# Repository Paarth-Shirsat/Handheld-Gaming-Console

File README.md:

# Handheld Gaming Console

---

A Custom STM32-based Board that runs simple games on an LCD, with various peripherals such as IMU, DF-Player Mini, Buttons, Joystick and a Power System.

## PCB Iterations
---
### OLD PCB
---

### NEW PCB
---

## Table Of Contents

---

- [About The Project](#about-the-project)
    - [Tech Stack](#tech-stack)
    - [File Structure](#file-structure)
- [Getting Started](#getting-started)
    - [Prerequisites](#prerequisites)
        - Hardware
        - Software
    - [Installation](#installation)
- [Usage](#usage)
- [Results And Demo](#results-and-demo)
- [Future Work](#future-work)
- [Contributors](#contributors)
- [Acknowledgements And Resources](#acknowledgements-and-resources)

## About The Project

---

The Handheld Gaming Console is a custom made Printed Circuit Board which utilizes STM32F407VGT6 as its MCU controlling all of the peripherals. The firmware involves setting up all the components and utilizing them to run simple games with the help of controlling hardware such as buttons, joystick and IMU.
The firmware for this project is a bare-metal implementation built on a Hardware Abstraction Layer (HAL). This project is designed to provide hands-on experience and a deep understanding of the embedded development workflow.

This repository will provide all the firmware, PCB files, and steps to use those.

### Tech Stack

---

### File Structure

---

```jsx
Handheld-Gaming-Console/
├── DFPLAYER/
│   ├── dfplayer.c
│   └── dfplayer.h
│
├── HANDHELD/
│   ├── ASSETS/
│   ├── DRIVERS/
│   ├── SRC/
│   └── README.md
│
├── HandHeld-Gaming-Console/
│   ├── .settings/
│   ├── Core/
│   ├── Debug/
│   ├── Drivers/
│   ├── .cproject
│   ├── .mxproject
│   ├── .project
│   ├── HandHeld-Gaming-Console.ioc
│   ├── STM32F407VGTX_FLASH.ld
│   └── STM32F407VGTX_RAM.ld
│
├── Handheld-Nucleo/
│   ├── .settings/
│   ├── Core/
│   ├── Debug/
│   ├── Drivers/
│   ├── CMSIS/
│   ├── GAME/
│   ├── GAME2/
│   ├── MPU6050/
│   ├── STM32F4xx_HAL_Driver/
│   ├── TFT/
│   ├── .cproject
│   ├── .mxproject
│   ├── .project
│   ├── Handheld-Nucleo Debug.launch
│   ├── Handheld-Nucleo.ioc
│   ├── STM32F401RETX_FLASH.ld
│   └── STM32F401RETX_RAM.ld
│
├── PCB Files/
│   ├── HGC PCB.kicad_pcb
│   ├── HGC PROJECT.kicad_pro
│   └── HGC SCHEMATIC.kicad_sch
│
├── UART/
│   ├── uart.c
│   └── uart.h
│
└── README.md
```

## Getting Started

---

### Prerequisites

---

- Hardware
    - STM32 Microcontroller (STM32 Bluepill or Nucleo-F401RE for development)
    - ST-Link V2 or USB-to-TTL adapter (for testing/debugging)
    - Display Driver: ILI9341
    - IMU: MPU6050 (Integrated 6-axis MotionTracking device)
    - MP3 Module: DF-Player Mini
    - Joystick and Buttons
    - Speaker
- Software
    - STM32CubeIDE
    - STM32CubeProgrammer
    - PuTTY (For Serial Monitor)
    - KiCad

### Installation

---

1. Clone the repository

```jsx
git clone https://github.com/Paarth-Shirsat/Handheld-Gaming-Console.git
```

## Usage

---

Steps to flash firmware

1. Connect the console (PCB) to your computer via USB to type C cable.
2. Start the STM32CubeProgrammer.
- By using UART
    1. Select ‘UART’ from the drop-down in the top right. Select the port and set baudrate to ‘115200’ Bd.
    2. Go to ‘Erasing & Programming’ section from the far left part.
    3. Select file path of the ‘.bin’ file from the project folder (search in the ‘Debug’ folder). 
    4. Now, set the BOOT0 pin to high by flicking the switch and click ‘Connect’.
    5. After connecting successfully, click on the ‘Start Programming’ option to start uploading the firmware. A few pop-ups would appear and the board will disconnect automatically.
    6. Now, set the BOOT0 pin to low by again flicking the switch to initial position. Press the ‘Reset’ button on the PCB. You can safely remove the USB to type C cable.
- By using ST-Link
    1. Select ‘UART’ from the drop-down in the top right. Select ‘Serial Number’ and set ‘Port’ as SWD (Serial Wire Debug).
    2. Go to ‘Erasing & Programming’ section from the far left part.
    3. Select file path of the ‘.bin’ file from the project folder (search in the ‘Debug’ folder). 
    4. After the pop-up for flashing of firmware successfully comes, you can safely remove the USB to type C cable.

## Results And Demo

---

Videos of working prototypes are as follows:

Video of Game’s working:

## Future Work

---

- [ ]  Addition of sound system

## Contributors

---

- [Ashish Nerlekar](https://github.com/ashish4225)
- [Mustafa T. R.](https://github.com/mt-tass)
- [Paarth Shirsat](https://github.com/Paarth-Shirsat)

## Acknowledgements And Resources

---

- SRA VJTI Eklavya 2025
- Mentors
    - [Vishal Mutha](https://github.com/Vishal-Mutha)
    - [Piyush Patle](https://github.com/PiyushPatle26)
    - [Shaurya Rane](https://github.com/shauryarane05)
- Resources
    - Datasheets for MCU and peripherals utilized.
    - Repository for ILI9341 Library: [Repository Link](https://github.com/afiskon/stm32-ili9341)

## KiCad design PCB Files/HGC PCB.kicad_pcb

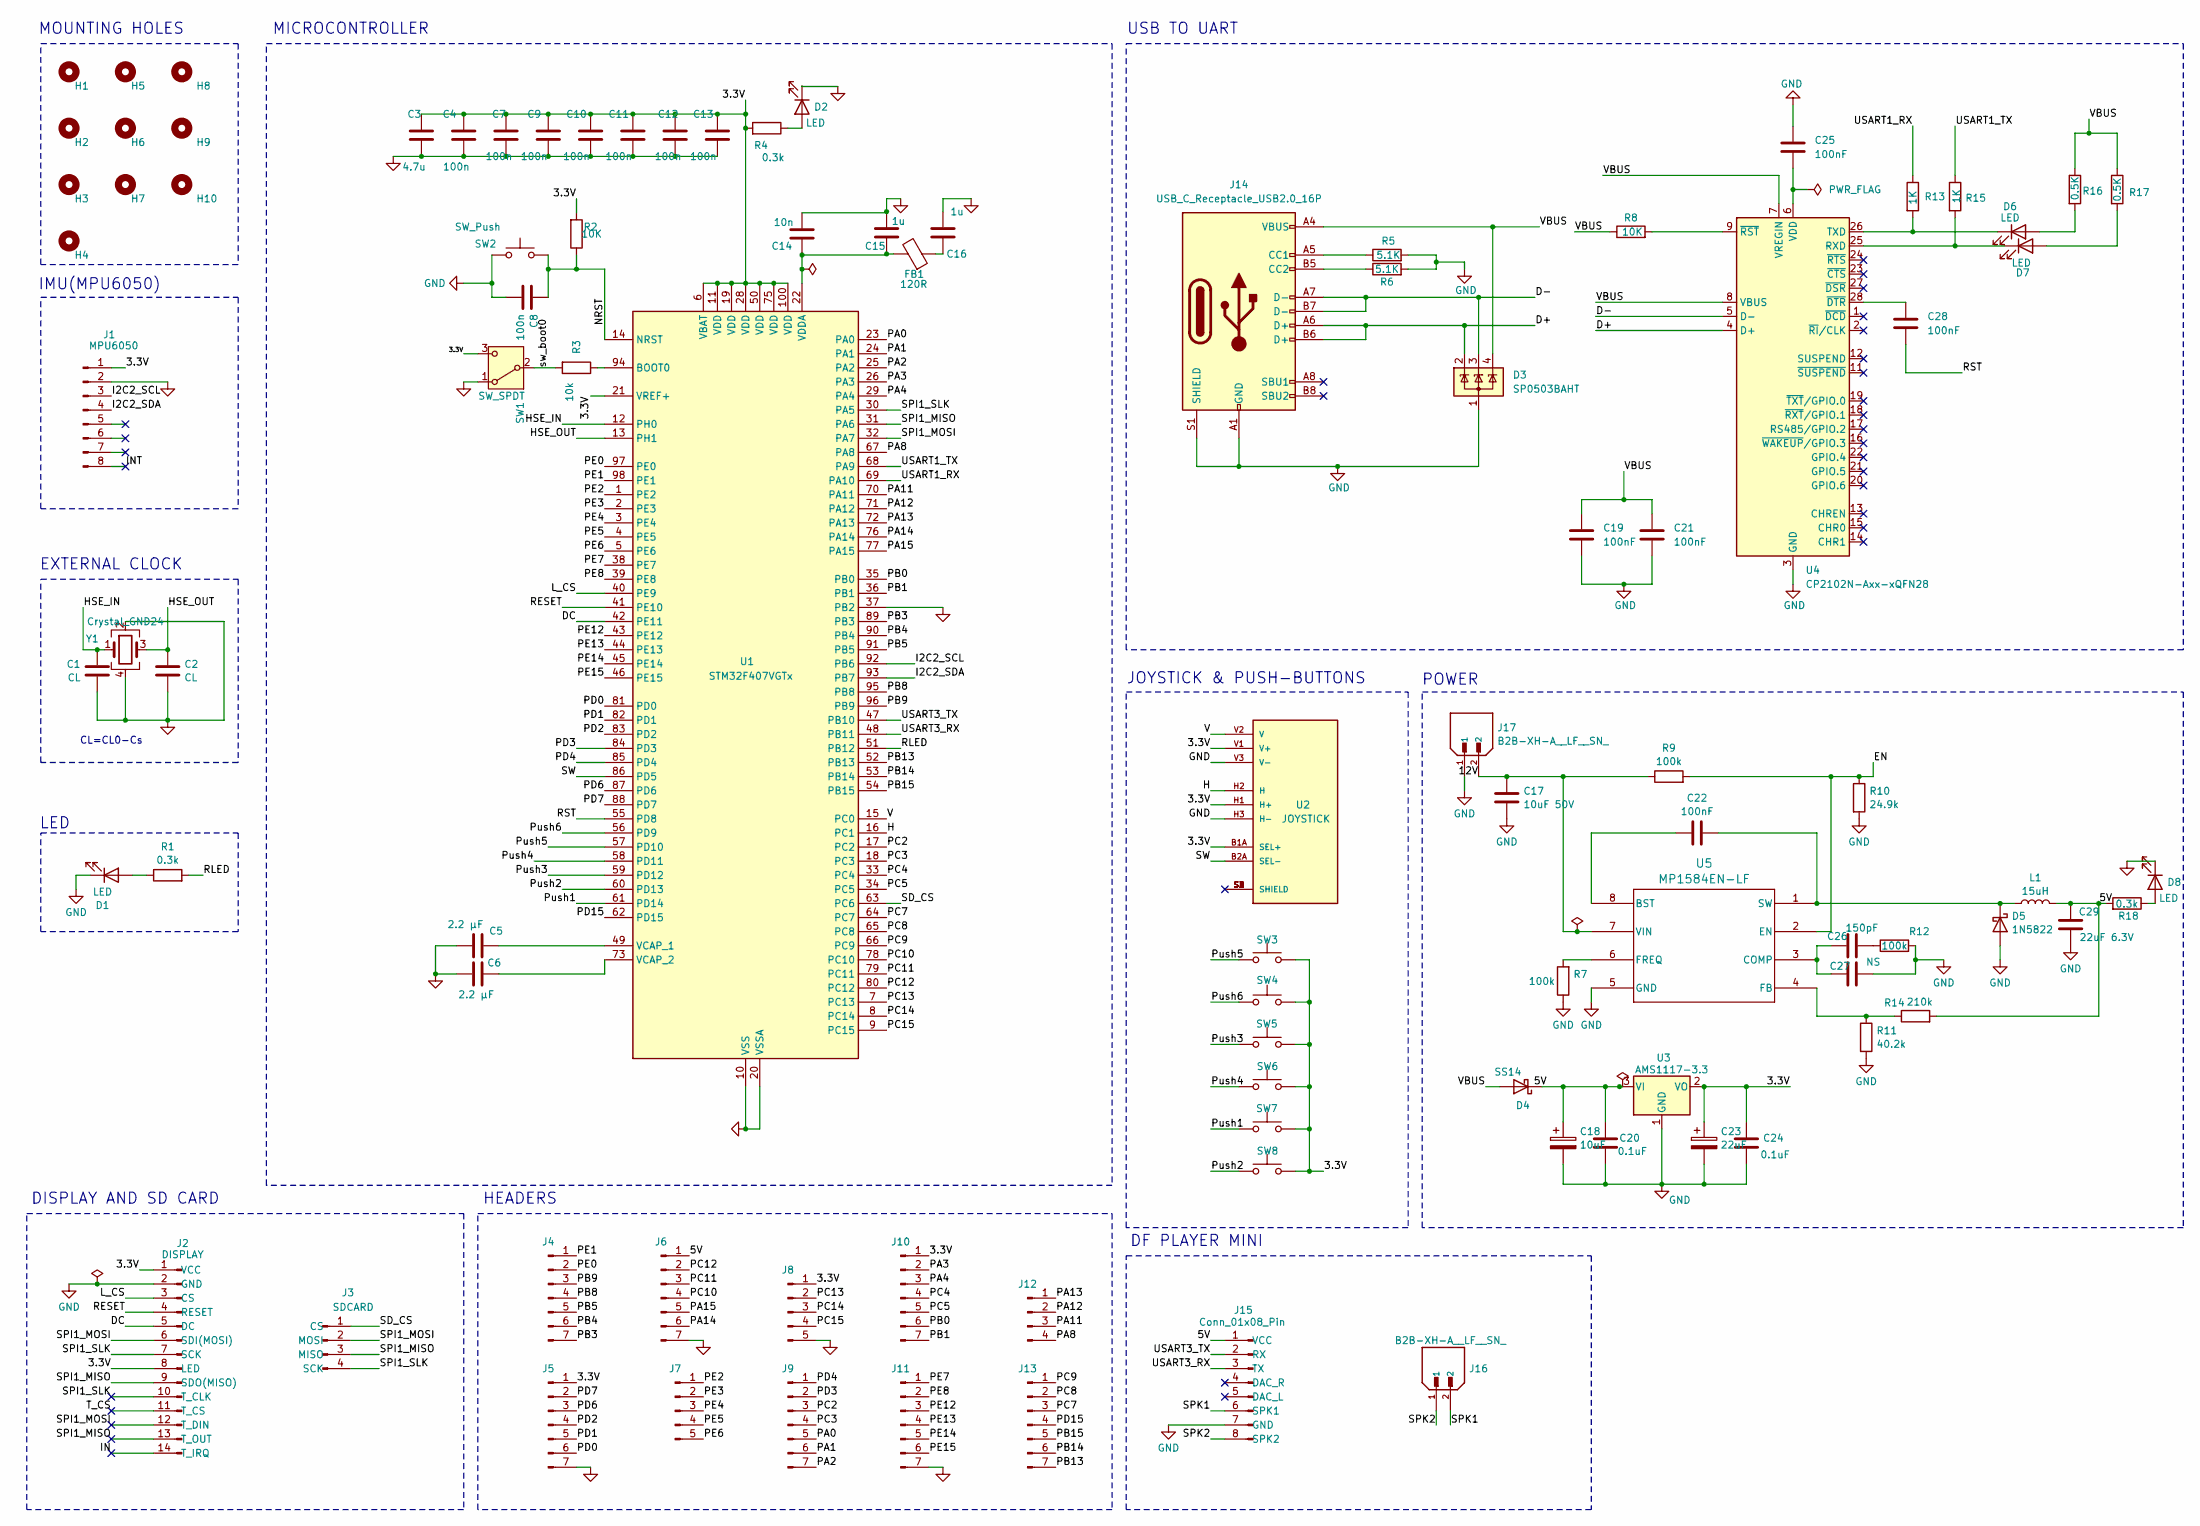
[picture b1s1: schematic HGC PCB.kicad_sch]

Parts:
C1, C2: CL; C_0805_2012Metric
C3: 4.7u; C_0805_2012Metric
C4, C7, C8, C9, C10, C11, C12, C13: 100n; C_0805_2012Metric
C5, C6: 2.2 µF; C_0805_2012Metric
C14: 10n; C_0805_2012Metric
C15, C16: 1u; C_0805_2012Metric
C17: 10uF 50V; C_0805_2012Metric
C18: 10uF; CP_EIA-3216-10_Kemet-I_HandSolder
C19, C21, C22, C25, C28: 100nF; C_0805_2012Metric
C20, C24: 0.1uF; C_0805_2012Metric
C23: 22uF; CP_EIA-3216-10_Kemet-I_HandSolder
C26: 150pF; C_0805_2012Metric
C27: NS; C_0805_2012Metric
C29: 22uF 6.3V; C_0805_2012Metric
D1, D2, D6, D7, D8: LED; LED_0805_2012Metric
D3: SP0503BAHT; SOT-143
D4: SS14; D_SMA
D5: 1N5822; D_SMA
FB1: 120R; L_0805_2012Metric
H1, H2, H3, H4, H5, H6, H7, H8, H9, H10: MountingHole; MountingHole_3.2mm_M3
J1: MPU6050; PinSocket_1x08_P2.54mm_Vertical
J2: DISPLAY; PinSocket_1x14_P2.54mm_Vertical
J3: SDCARD; PinSocket_1x04_P2.54mm_Vertical
J4, J5, J6, J9, J10, J11, J13: Conn_01x07_Pin; PinHeader_1x07_P2.54mm_Vertical
J7, J8: Conn_01x05_Pin; PinHeader_1x05_P2.54mm_Vertical
J12: Conn_01x04_Pin; PinHeader_1x04_P2.54mm_Vertical
J14: USB_C_Receptacle_USB2.0_16P; USB_C_Receptacle_HRO_TYPE-C-31-M-12
J15: Conn_01x08_Pin; JST_EH_S8B-EH_1x08_P2.50mm_Horizontal
J16, J17: B2B-XH-A__LF__SN_; JST_B2B-XH-A__LF__SN_; PARTREV N/A
L1: 15uH; L_0805_2012Metric
R1, R4, R18: 0.3k; R_0805_2012Metric
R2, R8: 10K; R_0805_2012Metric
R3: 10k; R_0805_2012Metric
R5, R6: 5.1K; R_0805_2012Metric
R7, R9, R12: 100k; R_0805_2012Metric
R10: 24.9k; R_0805_2012Metric
R11: 40.2k; R_0805_2012Metric
R13, R15: 1K; R_0805_2012Metric
R14: 210k; R_0805_2012Metric
R16, R17: 0.5K; R_0805_2012Metric
SW1: SW_SPDT; SW_SPDT_PCM12
SW2: SW_Push; SW_Push_SPST_NO_Alps_SKRK
SW3, SW4, SW5, SW6, SW7, SW8: SW_Push; SW_Push_1P1T_NO_CK_KSC7xxJ
U1: STM32F407VGTx; LQFP-100_14x14mm_P0.5mm
U2: JOYSTICK; XDCR_COM-09032; PARTREV N/A
U3: AMS1117-3.3; SOT-223-3_TabPin2
U4: CP2102N-Axx-xQFN28; QFN-28-1EP_5x5mm_P0.5mm_EP3.35x3.35mm
U5: MP1584EN-LF; SOIC8E_MPS
Y1: Crystal_GND24; Crystal_SMD_3225-4Pin_3.2x2.5mm

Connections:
/3.3V: C3.1, C4.1, C7.1, C9.1, C10.1, C11.1, C12.1, C13.1, C23.1, C24.1, J1.1, J2.1 (VCC), J2.8 (LED), J5.1, J8.1, J10.1, R2.2, R4.2, SW1.3 (C), SW3.1, SW4.1, SW5.1, SW6.1, SW7.1, SW8.1, U1.6 (VBAT), U1.11 (VDD), U1.19 (VDD), U1.21 (VREF+), U1.28 (VDD), U1.50 (VDD), U1.75 (VDD), U1.100 (VDD), U2.B1A (SEL+), U2.H1 (H+), U2.V1 (V+), U3.2 (VO)
/5V: C18.1, C20.1, C29.1, D4.1 (K), J6.1, J15.1 (VCC), L1.2, R14.2, R18.2, U3.3 (VI)
/12V: C17.1, J17.2, R9.1, U5.7 (VIN)
/D+: D3.2 (K), J14.A6 (D+), J14.B6 (D+), U4.4 (D+)
/D-: D3.3 (K), J14.A7 (D-), J14.B7 (D-), U4.5 (D-)
/DC: J2.5 (DC), U1.42 (PE11)
/EN: R9.2, R10.1, U5.2 (EN)
/H: U1.16 (PC1), U2.H2 (H)
/HSE_IN: C1.2, U1.12 (PH0), Y1.1
/HSE_OUT: C2.2, U1.13 (PH1), Y1.3
/I2C2_SCL: J1.3, U1.92 (PB6)
/I2C2_SDA: J1.4, U1.93 (PB7)
/IN: J2.14 (T_IRQ)
/INT: J1.8
/L_CS: J2.3 (CS), U1.40 (PE9)
/NRST: C8.2, R2.1, SW2.2, U1.14 (NRST); also elsewhere on the board
/PA0: J9.5, U1.23 (PA0)
/PA1: J9.6, U1.24 (PA1)
/PA2: J9.7, U1.25 (PA2)
/PA3: J10.2, U1.26 (PA3)
/PA4: J10.3, U1.29 (PA4)
/PA8: J12.4, U1.67 (PA8)
/PA11: J12.3, U1.70 (PA11)
/PA12: J12.2, U1.71 (PA12)
/PA13: J12.1, U1.72 (PA13)
/PA14: J6.6, U1.76 (PA14)
/PA15: J6.5, U1.77 (PA15)
/PB0: J10.6, U1.35 (PB0)
/PB1: J10.7, U1.36 (PB1)
/PB3: J4.7, U1.89 (PB3)
/PB4: J4.6, U1.90 (PB4)
/PB5: J4.5, U1.91 (PB5)
/PB8: J4.4, U1.95 (PB8)
/PB9: J4.3, U1.96 (PB9)
/PB13: J13.7, U1.52 (PB13)
/PB14: J13.6, U1.53 (PB14)
/PB15: J13.5, U1.54 (PB15)
/PC2: J9.3, U1.17 (PC2)
/PC3: J9.4, U1.18 (PC3)
/PC4: J10.4, U1.33 (PC4)
/PC5: J10.5, U1.34 (PC5)
/PC7: J13.3, U1.64 (PC7)
/PC8: J13.2, U1.65 (PC8)
/PC9: J13.1, U1.66 (PC9)
/PC10: J6.4, U1.78 (PC10)
/PC11: J6.3, U1.79 (PC11)
/PC12: J6.2, U1.80 (PC12)
/PC13: J8.2, U1.7 (PC13)
/PC14: J8.3, U1.8 (PC14)
/PC15: J8.4, U1.9 (PC15)
/PD0: J5.6, U1.81 (PD0)
/PD1: J5.5, U1.82 (PD1)
/PD2: J5.4, U1.83 (PD2)
/PD3: J9.2, U1.84 (PD3)
/PD4: J9.1, U1.85 (PD4)
/PD6: J5.3, U1.87 (PD6)
/PD7: J5.2, U1.88 (PD7)
/PD15: J13.4, U1.62 (PD15)
/PE0: J4.2, U1.97 (PE0)
/PE1: J4.1, U1.98 (PE1)
/PE2: J7.1, U1.1 (PE2)
/PE3: J7.2, U1.2 (PE3)
/PE4: J7.3, U1.3 (PE4)
/PE5: J7.4, U1.4 (PE5)
/PE6: J7.5, U1.5 (PE6)
/PE7: J11.1, U1.38 (PE7)
/PE8: J11.2, U1.39 (PE8)
/PE12: J11.3, U1.43 (PE12)
/PE13: J11.4, U1.44 (PE13)
/PE14: J11.5, U1.45 (PE14)
/PE15: J11.6, U1.46 (PE15)
/Push1: SW7.2, U1.61 (PD14)
/Push2: SW8.2, U1.60 (PD13)
/Push3: SW5.2, U1.59 (PD12)
/Push4: SW6.2, U1.58 (PD11)
/Push5: SW3.2, U1.57 (PD10)
/Push6: SW4.2, U1.56 (PD9)
/RESET: J2.4 (RESET), U1.41 (PE10)
/RLED: R1.2, U1.51 (PB12)
/RST: C28.1, U1.55 (PD8)
/SD_CS: J3.1 (CS), U1.63 (PC6)
/SPI1_MISO: J2.9 (SDO(MISO)), J2.13 (T_OUT), J3.3 (MISO), U1.31 (PA6)
/SPI1_MOSI: J2.6 (SDI(MOSI)), J2.12 (T_DIN), J3.2 (MOSI), U1.32 (PA7)
/SPI1_SLK: J2.7 (SCK), J2.10 (T_CLK), J3.4 (SCK), U1.30 (PA5)
/SPK1: J15.6 (SPK1), J16.2
/SPK2: J15.8 (SPK2), J16.1
/SW: U1.86 (PD5), U2.B2A (SEL-)
/T_CS: J2.11 (T_CS)
/USART1_RX: R13.1, U1.69 (PA10)
/USART1_TX: R15.1, U1.68 (PA9)
/USART3_RX: J15.3 (TX), U1.48 (PB11)
/USART3_TX: J15.2 (RX), U1.47 (PB10)
/V: U1.15 (PC0), U2.V2 (V)
/VBUS: C19.1, C21.1, D3.4 (K), D4.2 (A), J14.A4 (VBUS), J14.A9 (VBUS), J14.B4 (VBUS), J14.B9 (VBUS), R8.1, R16.1, R17.1, U4.7 (VREGIN), U4.8 (VBUS)
/sw_boot0: R3.2, SW1.2 (B)
GND: C1.1, C2.1, C3.2, C4.2, C5.2, C6.2, C7.2, C8.1, C9.2, C10.2, C11.2, C12.2, C13.2, C14.2, C15.2, C16.2, C17.2, C18.2, C19.2, C20.2, C21.2, C23.2, C24.2, C25.1, C27.2, C29.2, D1.1 (K), D2.1 (K), D3.1 (A), D5.2 (A), D8.1 (K), J1.2, J2.2 (GND), J5.7, J6.7, J8.5, J11.7, J14.A1 (GND), J14.A12 (GND), J14.B1 (GND), J14.B12 (GND), J14.S1 (SHIELD), J15.7 (GND), J17.1, R5.2, R6.2, R7.1, R10.2, R11.2, R12.2, SW1.1 (A), SW2.1, U1.10 (VSS), U1.20 (VSSA), U1.27 (VSS), U1.37 (PB2), U1.74 (VSS), U1.99 (VSS), U2.H3 (H-), U2.V3 (V-), U3.1 (GND), U4.3 (GND), U4.29 (GND), U5.5 (GND), Y1.2, Y1.4; also elsewhere on the board
unnamed: C16.1, FB1.1
unnamed: C26.2, R12.1
unnamed: D1.2 (A), R1.1
unnamed: D2.2 (A), R4.1
unnamed: C22.1, D5.1 (K), L1.1, U5.1 (SW)
unnamed: D6.2 (A), R16.2
unnamed: D6.1 (K), R13.2, U4.26 (TXD)
unnamed: D7.2 (A), R17.2
unnamed: D7.1 (K), R15.2, U4.25 (RXD)
unnamed: D8.2 (A), R18.1
unnamed: J14.A5 (CC1), R5.1
unnamed: J14.B5 (CC2), R6.1
unnamed: R3.1, U1.94 (BOOT0)
unnamed: C5.1, U1.49 (VCAP_1)
unnamed: C6.1, U1.73 (VCAP_2)
unnamed: C14.1, C15.1, FB1.2, U1.22 (VDDA)
unnamed: C25.2, U4.6 (VDD)
unnamed: C28.2, U4.28 (~DTR)
unnamed: R8.2, U4.9 (~RST)
unnamed: C22.2, U5.8 (BST)
unnamed: C26.1, C27.1, U5.3 (COMP)
unnamed: R11.1, R14.1, U5.4 (FB)
unnamed: R7.2, U5.6 (FREQ)

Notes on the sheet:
JOYSTICK & PUSH-BUTTONS
MOUNTING HOLES
DF PLAYER MINI
EXTERNAL CLOCK
MICROCONTROLLER
LED
DISPLAY AND SD CARD
USB TO UART
IMU(MPU6050)
HEADERS
CL=CL0-Cs
POWER

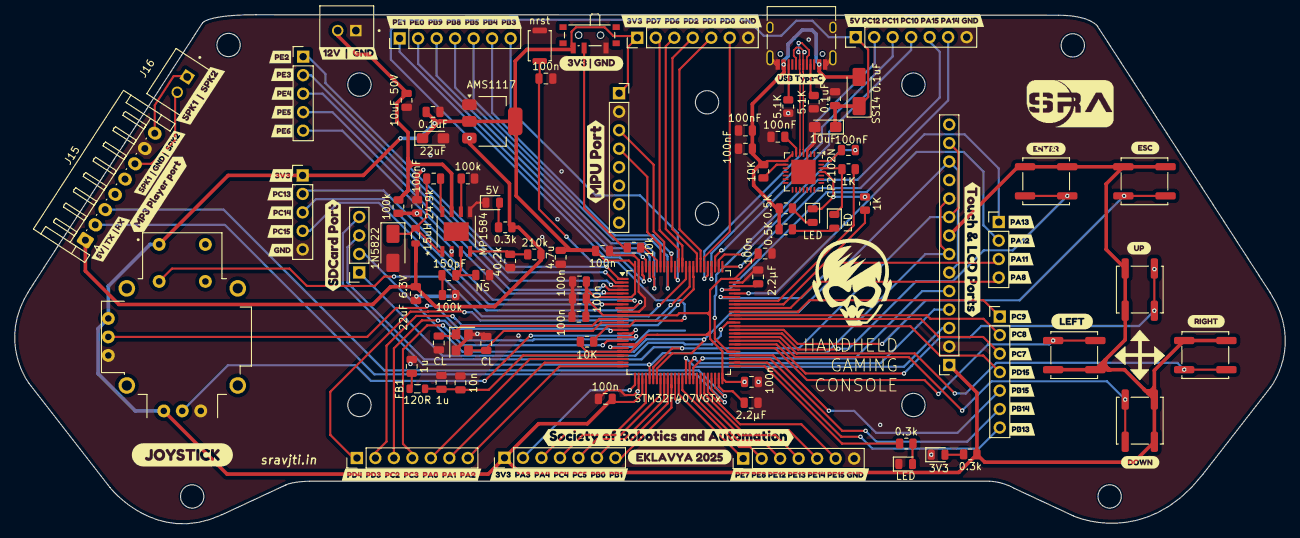
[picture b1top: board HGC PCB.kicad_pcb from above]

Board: 2 copper layers, 174.5 x 69.9 mm, 144 parts (1 on the bottom side), 116 nets.

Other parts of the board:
kibuzzard-68C92F98: G***; kibuzzard-68C92F98
kibuzzard-68C92FA3: G***; kibuzzard-68C92FA3
kibuzzard-68C92FAB: G***; kibuzzard-68C92FAB
kibuzzard-68C92FB6: G***; kibuzzard-68C92FB6
kibuzzard-68C92FBD: G***; kibuzzard-68C92FBD
kibuzzard-68C92FC5: G***; kibuzzard-68C92FC5
kibuzzard-68C92FCD: G***; kibuzzard-68C92FCD
kibuzzard-68C92FD9: G***; kibuzzard-68C92FD9
kibuzzard-68C92FE3: G***; kibuzzard-68C92FE3
kibuzzard-68C92FEC: G***; kibuzzard-68C92FEC
kibuzzard-68C92FF6: G***; kibuzzard-68C92FF6
kibuzzard-68C93B2B: G***; kibuzzard-68C93B2B
kibuzzard-68C93D93: G***; kibuzzard-68C93D93
kibuzzard-68C922D4: G***; kibuzzard-68C922D4
kibuzzard-68C923AF: G***; kibuzzard-68C923AF
kibuzzard-68C923C7: G***; kibuzzard-68C923C7
kibuzzard-68C930B6: G***; kibuzzard-68C930B6
kibuzzard-68C930DF: G***; kibuzzard-68C930DF
kibuzzard-68C930EB: G***; kibuzzard-68C930EB
kibuzzard-68C931DF: G***; kibuzzard-68C931DF
kibuzzard-68C9310A: G***; kibuzzard-68C9310A
kibuzzard-68C9319C: G***; kibuzzard-68C9319C
kibuzzard-68C9320A: G***; kibuzzard-68C9320A
kibuzzard-68C9322C: G***; kibuzzard-68C9322C
kibuzzard-68C9330F: G***; kibuzzard-68C9330F
kibuzzard-68C9333E: G***; kibuzzard-68C9333E
kibuzzard-68C92324: G***; kibuzzard-68C92324
kibuzzard-68C93061: G***; kibuzzard-68C93061
kibuzzard-68C93086: G***; kibuzzard-68C93086
kibuzzard-68C93097: G***; kibuzzard-68C93097
kibuzzard-68C93100: G***; kibuzzard-68C93100
kibuzzard-68C93116: G***; kibuzzard-68C93116
kibuzzard-68C93123: G***; kibuzzard-68C93123
kibuzzard-68C93223: G***; kibuzzard-68C93223
kibuzzard-68C93326: G***; kibuzzard-68C93326
kibuzzard-68C93356: G***; kibuzzard-68C93356
kibuzzard-68CBCDEB: G***; kibuzzard-68CBCDEB
kibuzzard-68CBF0D1: G***; kibuzzard-68CBF0D1
kibuzzard-68D3B1B5: G***; kibuzzard-68D3B1B5
kibuzzard-668FE423: G***; kibuzzard-668FE423
kibuzzard-675FDA6A: G***; kibuzzard-675FDA6A
kibuzzard-694FD5EF: G***; kibuzzard-694FD5EF
kibuzzard-694FDB00: G***; kibuzzard-694FDB00
kibuzzard-6946C61F: G***; kibuzzard-6946C61F
kibuzzard-6946C392: G***; kibuzzard-6946C392
kibuzzard-6946C401: G***; kibuzzard-6946C401
nrst: SW_Push; SW_Push_SPST_NO_Alps_SKRK

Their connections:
/NRST: nrst.2; also elsewhere on the board
GND: nrst.1; also elsewhere on the board

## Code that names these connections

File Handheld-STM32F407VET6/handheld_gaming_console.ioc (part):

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Mcu.Name=STM32F407V(E-G)Tx
Mcu.Package=LQFP100
Mcu.UserName=STM32F407VETx
PA10.Mode=Asynchronous
PA10.Signal=USART1_RX
PA5.Mode=Full_Duplex_Master
PA5.Signal=SPI1_SCK
PA6.Mode=Full_Duplex_Master
PA6.Signal=SPI1_MISO
PA7.Mode=Full_Duplex_Master
PA7.Signal=SPI1_MOSI
PA9.Mode=Asynchronous
PA9.Signal=USART1_TX
PB10.Mode=Asynchronous
PB10.Signal=USART3_TX
PB11.Mode=Asynchronous
PB11.Signal=USART3_RX
PB12.Signal=GPIO_Output
PB6.Mode=I2C
PB6.Signal=I2C1_SCL
PB7.Mode=I2C
PB7.Signal=I2C1_SDA
PC0.Signal=ADCx_IN10
PC1.Signal=ADCx_IN11
PC6.Signal=GPIO_Output
PD10.Signal=GPIO_Input
PD11.Signal=GPIO_Input
PD12.Signal=GPIO_Input
PD13.Signal=GPIO_Input
PD14.Signal=GPIO_Input
PD5.Signal=GPIO_Input
PD9.Signal=GPIO_Input
PE10.Signal=GPIO_Output
PE11.Signal=GPIO_Output
PE9.Signal=GPIO_Output
RCC.HSE_VALUE=25000000
RCC.SYSCLKFreq_VALUE=16000000
board=custom

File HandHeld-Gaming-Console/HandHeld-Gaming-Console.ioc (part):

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Mcu.Name=STM32F407V(E-G)Tx
Mcu.Package=LQFP100
Mcu.UserName=STM32F407VGTx
PA0-WKUP.Mode=Asynchronous
PA0-WKUP.Signal=UART4_TX
PA1.Mode=Asynchronous
PA1.Signal=UART4_RX
PA4.Signal=ADCx_IN4
PA6.Signal=ADCx_IN6
PB0.Signal=GPIO_Input
PB10.Mode=I2C
PB10.Signal=I2C2_SCL
PB11.Mode=I2C
PB11.Signal=I2C2_SDA
PB13.Mode=Full_Duplex_Master
PB13.Signal=SPI2_SCK
PB2.Signal=GPIO_Input
PC13-ANTI_TAMP.Signal=GPIO_Output
PC2.Mode=Full_Duplex_Master
PC2.Signal=SPI2_MISO
PC3.Mode=Full_Duplex_Master
PC3.Signal=SPI2_MOSI
PC4.Signal=GPIO_Input
PE10.Signal=GPIO_Input
PE12.Signal=GPIO_Input
PE4.Signal=GPIO_Output
PE6.Signal=GPIO_Output
PE8.Signal=GPIO_Input
PH0-OSC_IN.Mode=HSE-External-Oscillator
PH0-OSC_IN.Signal=RCC_OSC_IN
PH1-OSC_OUT.Mode=HSE-External-Oscillator
PH1-OSC_OUT.Signal=RCC_OSC_OUT
RCC.HSE_VALUE=25000000
RCC.SYSCLKFreq_VALUE=16000000
board=custom

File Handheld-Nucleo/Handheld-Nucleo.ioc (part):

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Mcu.Name=STM32F401R(D-E)Tx
Mcu.Package=LQFP64
Mcu.UserName=STM32F401RETx
PA0-WKUP.Signal=GPIO_Output
PA1.Signal=GPIO_Output
PA10.Signal=GPIO_Input
PA11.Signal=GPIO_Input
PA12.Signal=GPIO_Input
PA13.Signal=GPIO_Input
PA4.Signal=GPIO_Output
PA5.Mode=Full_Duplex_Master
PA5.Signal=SPI1_SCK
PA6.Mode=Full_Duplex_Master
PA6.Signal=SPI1_MISO
PA7.Mode=Full_Duplex_Master
PA7.Signal=SPI1_MOSI
PB0.Signal=ADCx_IN8
PB1.Signal=GPIO_Input
PB8.Mode=I2C
PB8.Signal=I2C1_SCL
PB9.Mode=I2C
PB9.Signal=I2C1_SDA
PC1.Signal=GPIO_Output
PC5.Signal=ADCx_IN15
PH0\ -\ OSC_IN.Mode=HSE-External-Oscillator
PH0\ -\ OSC_IN.Signal=RCC_OSC_IN
PH1\ -\ OSC_OUT.Mode=HSE-External-Oscillator
PH1\ -\ OSC_OUT.Signal=RCC_OSC_OUT
RCC.HSE_VALUE=25000000
RCC.SYSCLKFreq_VALUE=16000000
board=custom

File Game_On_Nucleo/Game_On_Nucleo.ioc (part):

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Mcu.Name=STM32F401R(D-E)Tx
Mcu.Package=LQFP64
Mcu.UserName=STM32F401RETx
PA3.Signal=ADCx_IN3
PA4.Signal=ADCx_IN4
PA5.Mode=Full_Duplex_Master
PA5.Signal=SPI1_SCK
PA6.Mode=Full_Duplex_Master
PA6.Signal=SPI1_MISO
PA7.Mode=Full_Duplex_Master
PA7.Signal=SPI1_MOSI
PB8.Mode=I2C
PB8.Signal=I2C1_SCL
PB9.Mode=I2C
PB9.Signal=I2C1_SDA
PC6.Signal=GPXTI6
PC7.Signal=GPXTI7
PC8.Signal=GPXTI8
PC9.Signal=GPXTI9
RCC.HSE_VALUE=25000000
RCC.SYSCLKFreq_VALUE=16000000
board=custom

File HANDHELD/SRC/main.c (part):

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  /*Configure GPIO pin Output Level */
  HAL_GPIO_WritePin(GPIOA, GPIO_PIN_0|GPIO_PIN_1|GPIO_PIN_4, GPIO_PIN_RESET);

  /*Configure GPIO pins : PC13 PC6 PC7 PC8
                           PC10 PC11 PC12 */
  GPIO_InitStruct.Pin = GPIO_PIN_13|GPIO_PIN_6|GPIO_PIN_7|GPIO_PIN_8
                          |GPIO_PIN_10|GPIO_PIN_11|GPIO_PIN_12;
  GPIO_InitStruct.Mode = GPIO_MODE_INPUT;
  GPIO_InitStruct.Pull = GPIO_NOPULL;
  HAL_GPIO_Init(GPIOC, &GPIO_InitStruct);

  /*Configure GPIO pins : PA0 PA1 PA4 */
  GPIO_InitStruct.Pin = GPIO_PIN_0|GPIO_PIN_1|GPIO_PIN_4;
  GPIO_InitStruct.Mode = GPIO_MODE_OUTPUT_PP;
  GPIO_InitStruct.Pull = GPIO_NOPULL;
  GPIO_InitStruct.Speed = GPIO_SPEED_FREQ_LOW;
  HAL_GPIO_Init(GPIOA, &GPIO_InitStruct);

  /*Configure GPIO pin : PB2 */
  GPIO_InitStruct.Pin = GPIO_PIN_2;
  GPIO_InitStruct.Mode = GPIO_MODE_INPUT;
  GPIO_InitStruct.Pull = GPIO_NOPULL;
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
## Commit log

2025-08-24 Library for MPU6050
2025-08-24 Game on Nucleo (Without MPU)
2025-09-07 Added Hardware Files
2025-09-07 Deleted some files
2025-09-07 updated ASSETS
2025-09-07 update video
2025-09-07 updating assets
2025-09-07 update gif
2025-09-07 update assets
2025-09-19 Update README.md
    fixing the table of contents issue
2025-09-23 pcb updated
2025-09-23 pcb updated again
2025-09-23 pcb updated for final review
2026-02-05 porting to vet6

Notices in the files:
HANDHELD/SRC/main.c:
Copyright (c) 2025 STMicroelectronics.
All rights reserved.
This software is licensed under terms that can be found in the LICENSE file
